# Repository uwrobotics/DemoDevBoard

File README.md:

# DemoDevBoard

## Reference Design

https://github.com/AstraThreshold/astra-launcher

## Microcontroller Selection

Main Microcontroller: https://www.digikey.com/en/products/detail/stmicroelectronics/STM32H533CET6/22519691

Aux Microcontroller: https://www.digikey.com/en/products/detail/nordic-semiconductor-asa/NRF52810-QCAA-R/13572776 (M4 + BLE)

USB to UART: FT230XQ

Battery charging: https://www.analog.com/media/en/technical-documentation/data-sheets/MAX14748.pdf

Need better FTDI Chip support

OLED Display: https://www.adafruit.com/product/5228

Optionally add-on board: https://www.digikey.com/en/product-highlight/l/lattice/ice40-ultraplus-fpga

## Issue

does the board need to in nature support oled display and how to configure two microcontroller boards

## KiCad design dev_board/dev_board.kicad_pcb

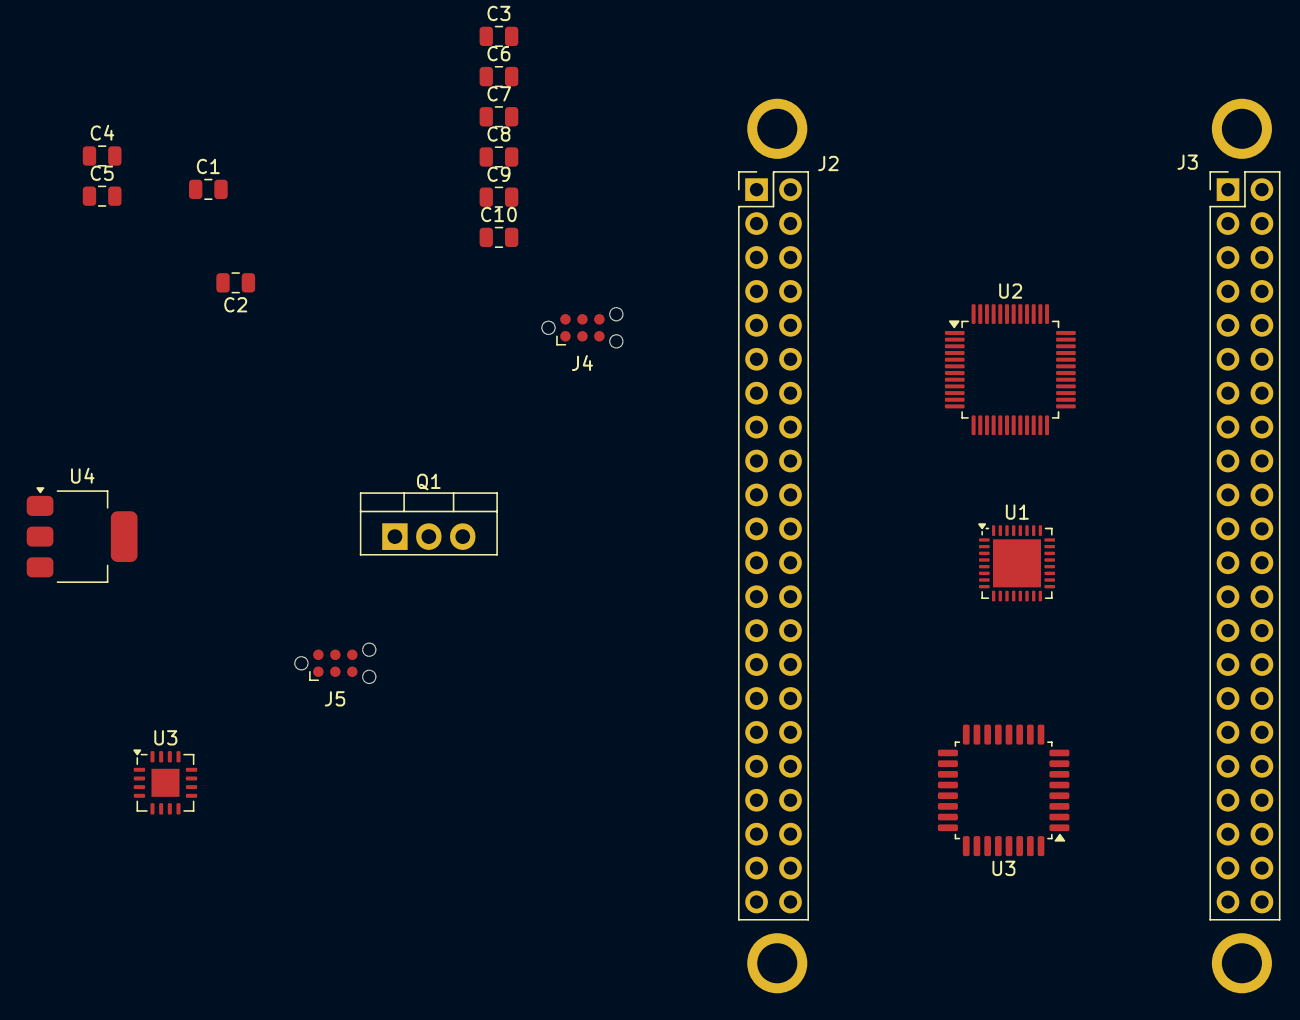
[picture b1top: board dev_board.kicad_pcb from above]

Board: 2 copper layers, 24 parts (0 on the bottom side), 11 nets, no tracks yet.

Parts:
C1, C2: 2.2uF; C_0805_2012Metric
C3: 4.7uF; C_0805_2012Metric
C4, C8: 1uF; C_0805_2012Metric
C5, C6, C7, C9, C10: 100nF; C_0805_2012Metric
H1, H2, H3, H4: MountingHole_Pad; MountingHole_3mm_Pad
J2: Left; PinHeader_2x22_P2.54mm_Vertical
J3: Right; PinHeader_2x22_P2.54mm_Vertical
J4, J5: Conn_ARM_SWD_TagConnect_TC2030-NL; Tag-Connect_TC2030-IDC-NL_2x03_P1.27mm_Vertical
Q1: BUT11; TO-220-3_Vertical
U1: nRF52810-QCxx; QFN-32-1EP_5x5mm_P0.5mm_EP3.6x3.6mm
U2: STM32H533CETx; LQFP-48_7x7mm_P0.5mm
U3: FT230XQ; QFN-16-1EP_4x4mm_P0.65mm_EP2.1x2.1mm
U3#2: FT232BM; LQFP-32_7x7mm_P0.8mm
U4: LT1963AxST-3.3; SOT-223-3_TabPin2

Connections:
+3V0: U3.1 (VCCIO), U3.8 (3V3OUT), U3.9 (~RESET)
+3V3: C3.1, C6.1, C7.1, C8.1, C9.1, C10.1, Q1.1 (B), U1.9 (VDD), U1.25 (VDD), U1.32 (VDD), U2.9 (VDDA), U2.24 (VDD), U2.36 (VDD), U2.48 (VDD), U4.3 (OUT)
+BATT: C4.1, C5.1, U2.1 (VBAT)
/aux_mcu/RST1: J5.3 (~RESET), U1.16 (P0.21/~RESET)
/main_mcu/BOOT: Q1.2 (C), U2.44 (BOOT0)
/main_mcu/RST: J4.3 (~RESET), U2.7 (NRST)
GND: C1.2, C2.1, C3.2, C4.2, C5.2, C6.2, C7.2, C8.2, C9.2, C10.2, Q1.3 (E), U1.20 (VSS), U1.29 (VSS), U1.33 (VSS), U2.8 (VSSA), U2.23 (VSS), U2.35 (VSS), U2.47 (VSS), U3.3 (GND), U3.13 (GND), U3.17 (GND), U4.2 (GND)
GNDD: H1.1, H2.1, H3.1, H4.1
unnamed: C1.1, U2.46 (VCAP)
unnamed: C2.2, U2.22 (VCAP)
VCC: U3.10 (VCC), U4.1 (IN)
